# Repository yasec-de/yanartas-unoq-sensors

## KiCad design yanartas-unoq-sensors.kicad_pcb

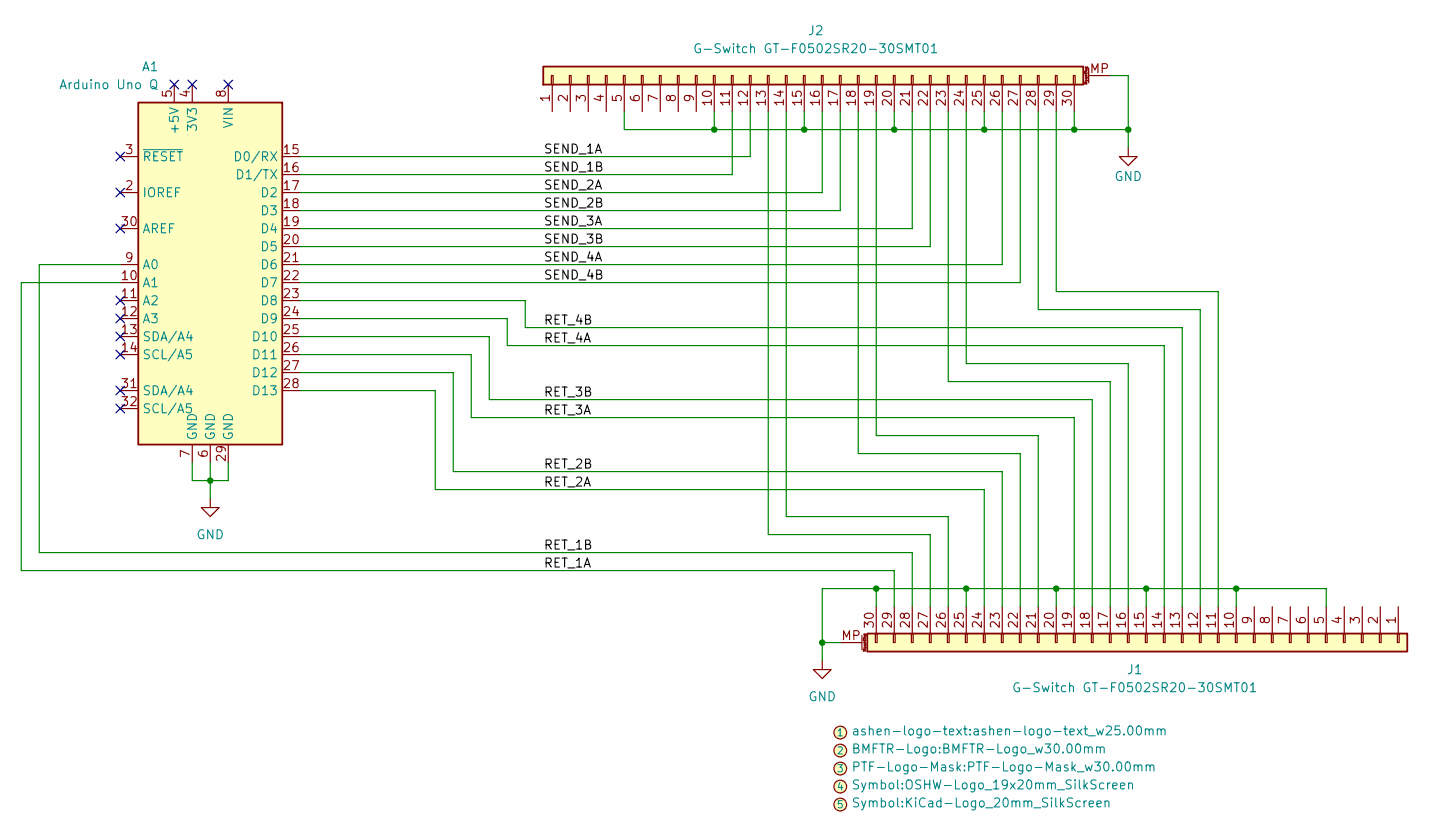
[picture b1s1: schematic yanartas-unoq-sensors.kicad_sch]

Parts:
A1: Arduino Uno Q; Arduino_UNO_R3
J1, J2: G-Switch GT-F0502SR20-30SMT01; FFC_30x0.5_ANY

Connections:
/RET_1A: A1.10 (A1), J1.29
/RET_1B: A1.9 (A0), J1.28
/RET_2A: A1.28 (D13), J1.24
/RET_2B: A1.27 (D12), J1.23
/RET_3A: A1.26 (D11), J1.19
/RET_3B: A1.25 (D10), J1.18
/RET_4A: A1.24 (D9), J1.14
/RET_4B: A1.23 (D8), J1.13
/SEND_1A: A1.15 (D0/RX), J2.12
/SEND_1B: A1.16 (D1/TX), J2.11
/SEND_2A: A1.17 (D2), J2.16
/SEND_2B: A1.18 (D3), J2.17
/SEND_3A: A1.19 (D4), J2.21
/SEND_3B: A1.20 (D5), J2.22
/SEND_4A: A1.21 (D6), J2.26
/SEND_4B: A1.22 (D7), J2.27
GND: A1.6 (GND), A1.7 (GND), A1.29 (GND), J1.5, J1.10, J1.15, J1.20, J1.25, J1.30, J1.MP (MountPin), J2.5, J2.10, J2.15, J2.20, J2.25, J2.30, J2.MP (MountPin)
unnamed: J1.11, J2.29
unnamed: J1.12, J2.28
unnamed: J1.16, J2.24
unnamed: J1.17, J2.23
unnamed: J1.21, J2.19
unnamed: J1.22, J2.18
unnamed: J1.26, J2.14
unnamed: J1.27, J2.13

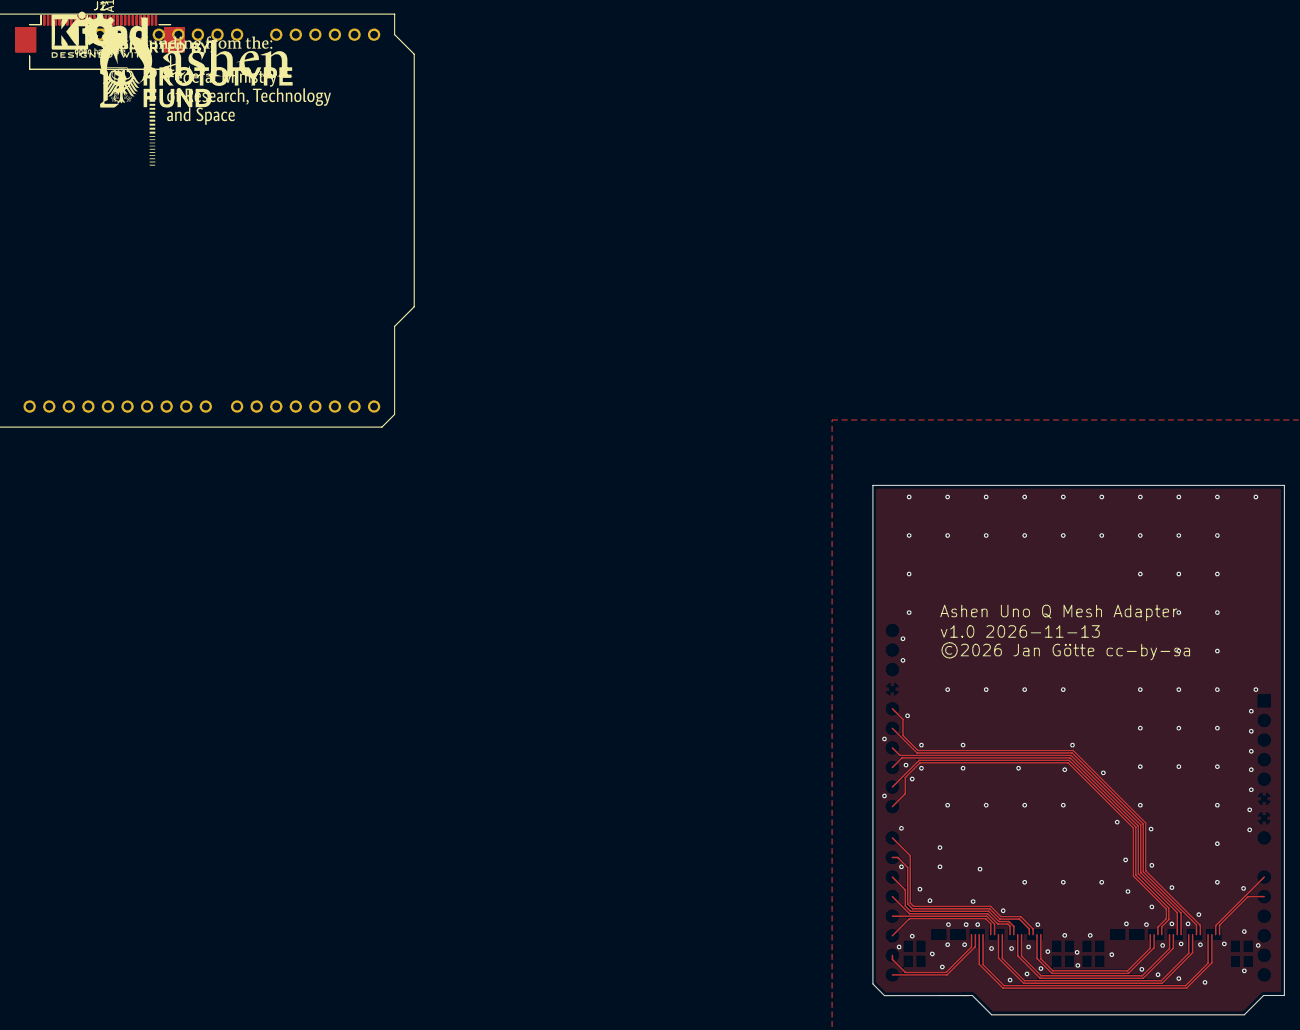
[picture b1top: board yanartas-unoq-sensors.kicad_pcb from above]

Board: 2 copper layers, 53.4 x 68.7 mm, 6 parts (0 on the bottom side), 25 nets.

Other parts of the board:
BMFTR-Logo_w30.00mm: G*****; BMFTR-Logo_w30.00mm
PTF-Logo-Mask_w30.00mm: G*****; PTF-Logo-Mask_w25.00mm
ashen-logo-text_w25.00mm: G*****; ashen-logo-text_w25.00mm

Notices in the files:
yanartas-unoq-sensors.kicad_pcb:
©2026 Jan Götte cc-by-sa
